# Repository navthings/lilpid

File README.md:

lilpid

a rocket that balances itself. building for hack club fallen (shenzhen, dec 2026)

my project is a self adjusting rocket model using a edf and pid self corectting gimabl movement. it sits on a stand with a pivot, you push it over and the gimbal swings the fan to shove it back upright

how to use

pip install pygame then python main.py, grab the rocket with ur mouse and flick it, the pid catches it
print stuff is in print/ (plates are 3mf, single parts in print/parts), cad is in cad/
pcb gerbers are controller/controller-gerbers.zip, just upload to jlc
parts are in bom.csv

why i made it

i made lilpid since ive always been interested in bps.space, flying, and rocketry, and wanted a excuse for the ridiculously expensive project to come to life

full assembly

pcb

schematic

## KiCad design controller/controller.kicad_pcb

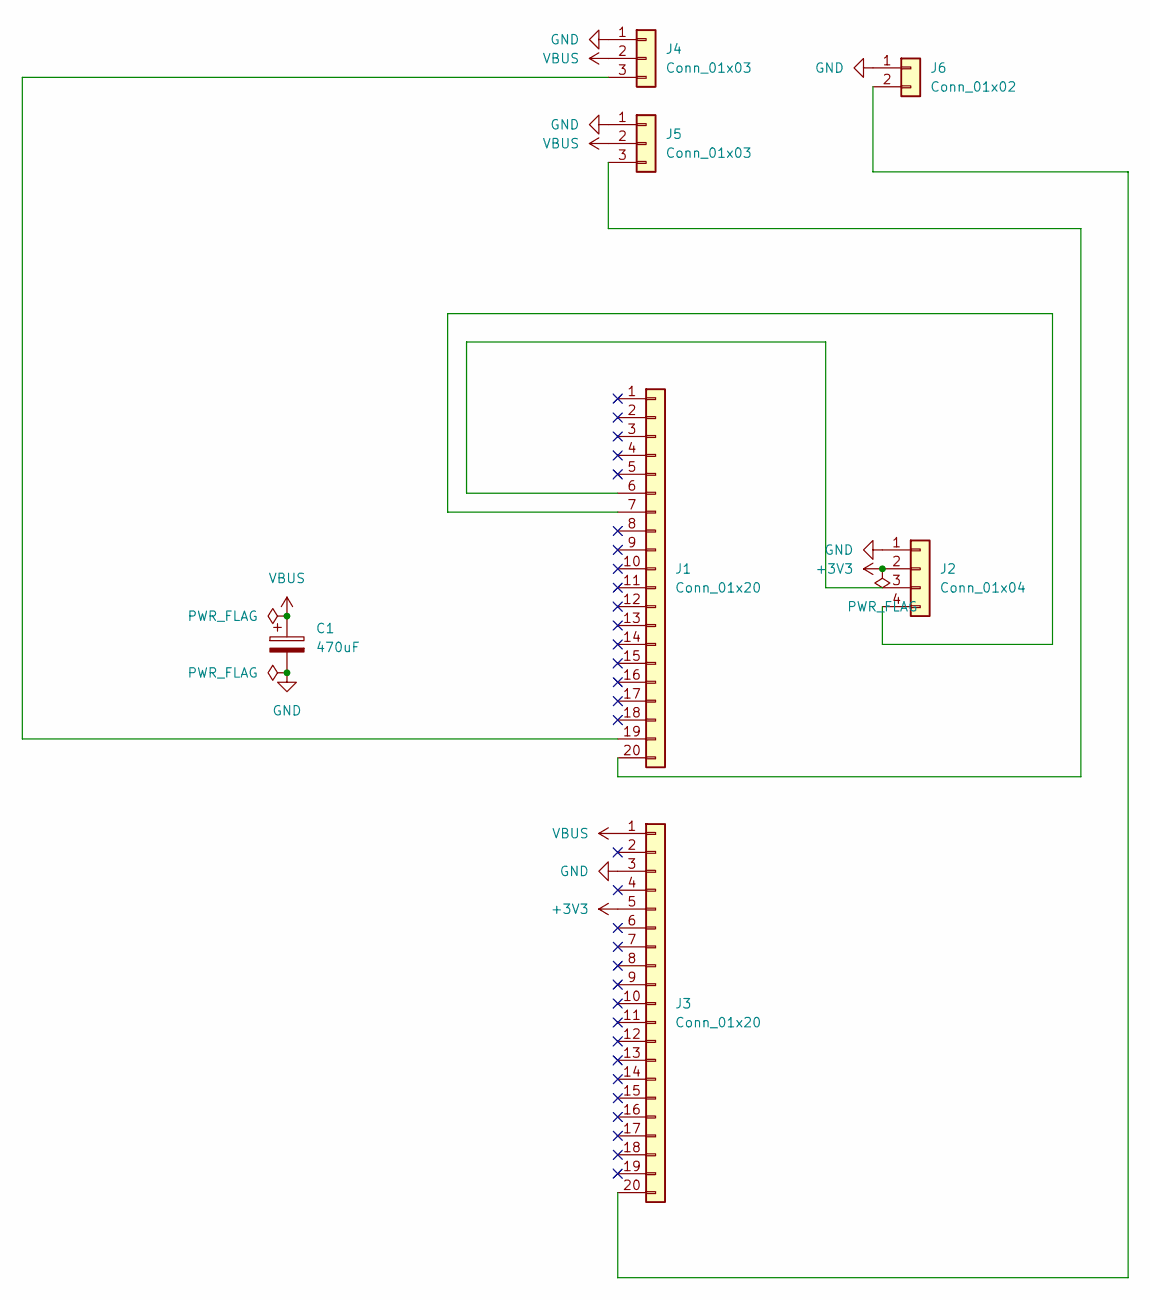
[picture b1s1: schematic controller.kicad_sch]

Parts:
C1: 470uF; CP_Radial_D8.0mm_P3.50mm
J1, J3: Conn_01x20; PinHeader_1x20_P2.54mm_Vertical
J2: Conn_01x04; PinHeader_1x04_P2.54mm_Vertical
J4, J5: Conn_01x03; PinHeader_1x03_P2.54mm_Vertical
J6: Conn_01x02; PinHeader_1x02_P2.54mm_Vertical

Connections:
+3V3: J2.2, J3.5
GND: C1.2, J2.1, J3.3, J4.1, J5.1, J6.1
unnamed: J1.6, J2.3
unnamed: J1.7, J2.4
unnamed: J1.19, J4.3
unnamed: J1.20, J5.3
unnamed: J3.20, J6.2
VBUS: C1.1, J3.1, J4.2, J5.2

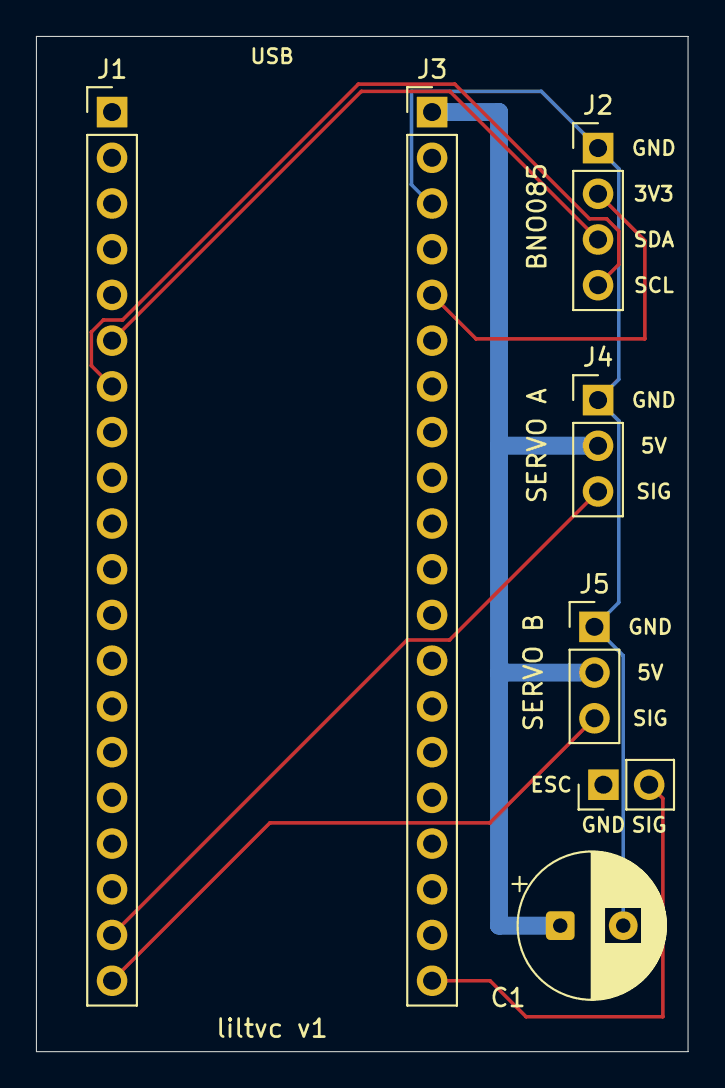
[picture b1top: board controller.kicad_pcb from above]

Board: 2 copper layers, 36.2 x 56.4 mm, 7 parts (0 on the bottom side), 8 nets.

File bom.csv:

"Item","Qty","Supplier","SKU","Unit (AUD)","Total (AUD)","Why"
"Raspberry Pi Pico 2H (with headers)","2","Core Electronics","CE10154","9.90","19.80","flight controller, solders onto the carrier PCB (J1/J3); 1 spare"
"Adafruit BNO085 9-DOF IMU","2","Core Electronics","ADA4754","46.45","92.90","measures the rocket's tilt (fused orientation) so the PID knows how far off vertical it is; 1 spare"
"JST SH 4-pin to male header cable 150mm","2","Core Electronics","ADA4209","1.95","3.90","connects the BNO085 to J2 on the PCB"
"FS90MG metal gear micro servo","4","Core Electronics","CE09378","7.40","29.60","2 servos drive the nozzle gimbal (pitch + yaw); 2 spares"
"Full-size breadboard","1","Core Electronics","PRT-12615","15.15","15.15","testing the IMU + servos before soldering the PCB"
"Jumper wire kit 140pcs","1","Core Electronics","CE05631","7.95","7.95","breadboard wiring"
"Jumper wire ribbon M/M 40pcs","1","Core Electronics","CE08574","3.95","3.95","breadboard wiring"
"Electrolytic capacitor pack (120pcs)","1","Core Electronics","CE05130","2.40","2.40","C1 470uF bulk cap on the servo power rail"
"Male pin header 1x40","1","Core Electronics","CE07828","0.45","0.45","servo headers J4/J5 on the PCB"
"HS-02 USB-C soldering iron (basic)","1","Core Electronics","CE10553","69.35","69.35","no soldering iron yet; needed to build the PCB"
"60/40 rosin core solder 0.8mm 200g","1","Core Electronics","AT1100","33.70","33.70","solder for the PCB"
"Solder wick","1","Core Electronics","TOL-09327","5.55","5.55","fixing solder mistakes"
"USB power bank 5000mAh","1","Core Electronics","AD0505B","26.95","26.95","powers the demo untethered at the showcase"
"Bambu Lab PLA 1.75mm 1kg (pick colour)","1","Core Electronics","CE10563","35.99","35.99","prints the body tube, stand + pivot, gimbal rings, servo mounts and nose cone (~500g incl. reprints)"
"Controller PCB 2-layer 36x56mm (5 pcs)","1","JLCPCB","controller-gerbers.zip","20.00","20.00","custom carrier board for the Pico, IMU and servos (estimate, check JLC quote + shipping)"
"TOTAL","","","","","367.64","plus Core shipping (quoted at checkout)"
